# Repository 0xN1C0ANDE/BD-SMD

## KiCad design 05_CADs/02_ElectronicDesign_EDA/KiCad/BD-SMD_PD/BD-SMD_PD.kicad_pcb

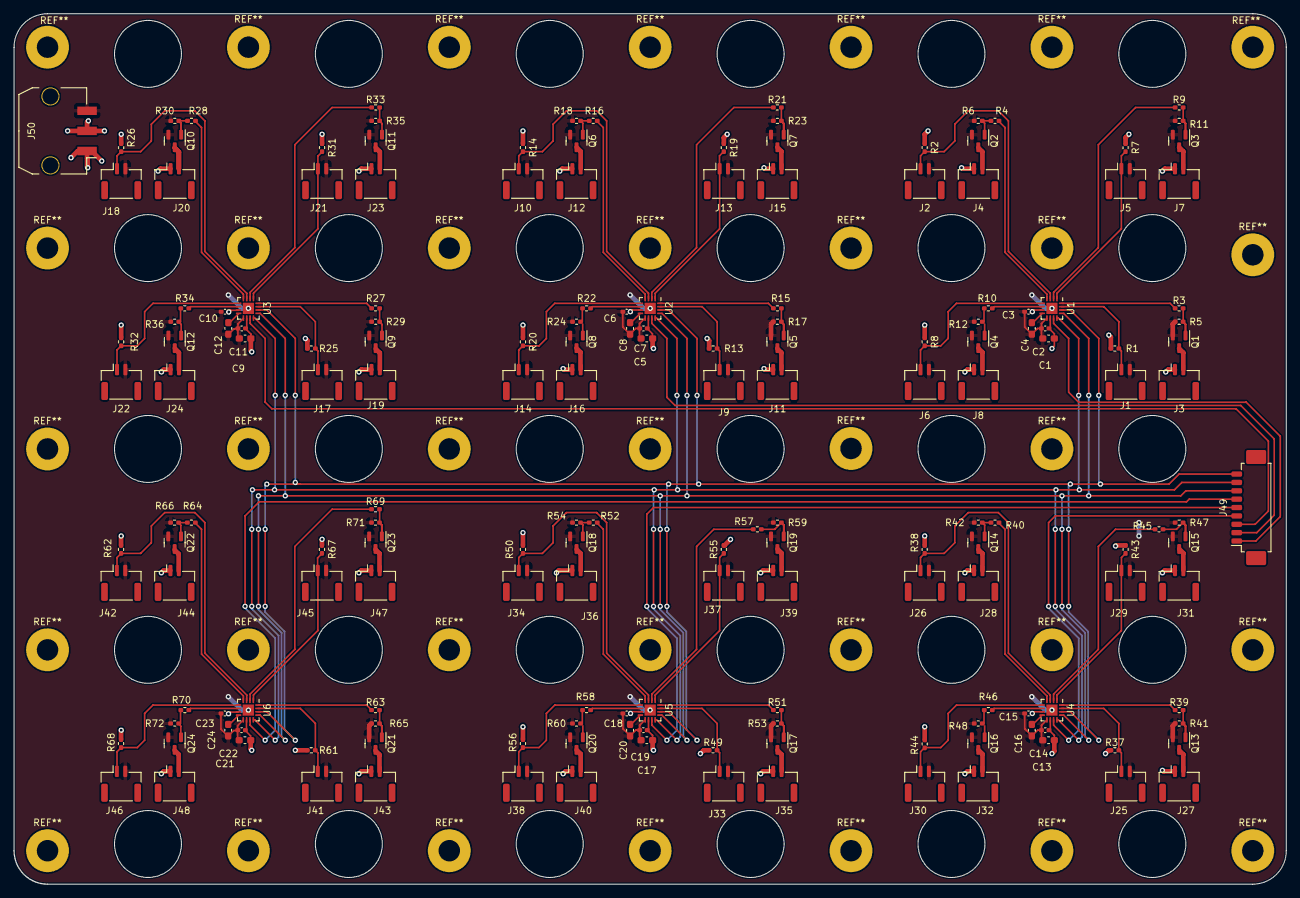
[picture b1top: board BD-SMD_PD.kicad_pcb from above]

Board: 2 copper layers, 190.0 x 130.0 mm, 176 parts (0 on the bottom side), 114 nets.

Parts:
C1, C4, C5, C8, C9, C12, C13, C16, C17, C20, C21, C24: 1u; C_0603_1608Metric_Pad1.08x0.95mm_HandSolder
C2, C3, C6, C7, C10, C11, C14, C15, C18, C19, C22, C23: 100n; C_0402_1005Metric_Pad0.74x0.62mm_HandSolder
J1, J2, J5, J6, J9, J10, J13, J14, J17, J18, J21, J22, J25, J26, J29, J30, J33, J34, J37, J38, J41, J42, J45, J46: Conn_01x02_sens; JST_GH_SM02B-GHS-TB_1x02-1MP_P1.25mm_Horizontal
J3, J4, J7, J8, J11, J12, J15, J16, J19, J20, J23, J24, J27, J28, J31, J32, J35, J36, J39, J40, J43, J44, J47, J48: Conn_01x02_heater; JST_GH_SM02B-GHS-TB_1x02-1MP_P1.25mm_Horizontal
J49: Conn_01x09; Molex_PicoBlade_53261-0971_1x09-1MP_P1.25mm_Horizontal
J50: Conn_01x03; Molex_Micro-Fit_3.0_43650-0310_1x03-1MP_P3.00mm_Horizontal
Q1, Q2, Q3, Q4, Q5, Q6, Q7, Q8, Q9, Q10, Q11, Q12, Q13, Q14, Q15, Q16, Q17, Q18, Q19, Q20, Q21, Q22, Q23, Q24: DMG3418L; SOT-23
R1, R2, R7, R8, R13, R14, R19, R20, R25, R26, R31, R32, R37, R38, R43, R44, R49, R50, R55, R56, R61, R62, R67, R68: 10k; R_0402_1005Metric_Pad0.72x0.64mm_HandSolder
R3, R4, R9, R10, R15, R16, R21, R22, R27, R28, R33, R34, R39, R40, R45, R46, R51, R52, R57, R58, R63, R64, R69, R70: 1k; R_0402_1005Metric_Pad0.72x0.64mm_HandSolder
R5, R6, R11, R12, R17, R18, R23, R24, R29, R30, R35, R36, R41, R42, R47, R48, R53, R54, R59, R60, R65, R66, R71, R72: 100k; R_0402_1005Metric_Pad0.72x0.64mm_HandSolder
U1, U2, U3, U4, U5, U6: ADS7028; WQFN-16-1EP_3x3mm_P0.5mm_EP1.68x1.68mm

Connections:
3.3V: C1.1, C2.1, C3.1, C5.1, C6.1, C7.1, C9.1, C10.1, C11.1, C13.1, C14.1, C15.1, C17.1, C18.1, C19.1, C21.1, C22.1, C23.1, J50.2, R1.1, R2.1, R7.1, R8.1, R13.1, R14.1, R19.1, R20.1, R25.1, R26.1, R31.1, R32.1, R37.1, R38.1, R43.1, R44.1, R49.1, R50.1, R55.1, R56.1, R61.1, R62.1, R67.1, R68.1, U1.7 (AVDD), U1.10 (DVDD), U2.7 (AVDD), U2.10 (DVDD), U3.7 (AVDD), U3.10 (DVDD), U4.7 (AVDD), U4.10 (DVDD), U5.7 (AVDD), U5.10 (DVDD), U6.7 (AVDD), U6.10 (DVDD)
24V: J3.1, J4.1, J7.1, J8.1, J11.1, J12.1, J15.1, J16.1, J19.1, J20.1, J23.1, J24.1, J27.1, J28.1, J31.1, J32.1, J35.1, J36.1, J39.1, J40.1, J43.1, J44.1, J47.1, J48.1, J50.1
/CS_0: J49.1, U1.11 (~CS)
/CS_1: J49.2, U2.11 (~CS)
/CS_2: J49.3, U3.11 (~CS)
/CS_3: J49.4, U4.11 (~CS)
/CS_4: J49.5, U5.11 (~CS)
/CS_5: J49.6, U6.11 (~CS)
/SCLK: J49.7, U1.13 (SCLK), U2.13 (SCLK), U3.13 (SCLK), U4.13 (SCLK), U5.13 (SCLK), U6.13 (SCLK)
/SDI: J49.9, U1.14 (SDI), U2.14 (SDI), U3.14 (SDI), U4.14 (SDI), U5.14 (SDI), U6.14 (SDI)
/SDO: J49.8, U1.12 (SDO), U2.12 (SDO), U3.12 (SDO), U4.12 (SDO), U5.12 (SDO), U6.12 (SDO)
/unit0/AIN0.0: J1.1, R1.2, U1.15 (AIN0)
/unit0/AIN1.0: R3.1, U1.16 (AIN1)
/unit0/AIN2.0: J5.1, R7.2, U1.1 (AIN2)
/unit0/AIN3.0: R9.1, U1.2 (AIN3)
/unit0/AIN4.0: J2.1, R2.2, U1.3 (AIN4)
/unit0/AIN5.0: R4.1, U1.4 (AIN5)
/unit0/AIN6.0: J6.1, R8.2, U1.5 (AIN6)
/unit0/AIN7.0: R10.1, U1.6 (AIN7)
/unit1/AIN0.0: J9.1, R13.2, U2.15 (AIN0)
/unit1/AIN1.0: R15.1, U2.16 (AIN1)
/unit1/AIN2.0: J13.1, R19.2, U2.1 (AIN2)
/unit1/AIN3.0: R21.1, U2.2 (AIN3)
/unit1/AIN4.0: J10.1, R14.2, U2.3 (AIN4)
/unit1/AIN5.0: R16.1, U2.4 (AIN5)
/unit1/AIN6.0: J14.1, R20.2, U2.5 (AIN6)
/unit1/AIN7.0: R22.1, U2.6 (AIN7)
/unit2/AIN0.0: J17.1, R25.2, U3.15 (AIN0)
/unit2/AIN1.0: R27.1, U3.16 (AIN1)
/unit2/AIN2.0: J21.1, R31.2, U3.1 (AIN2)
/unit2/AIN3.0: R33.1, U3.2 (AIN3)
/unit2/AIN4.0: J18.1, R26.2, U3.3 (AIN4)
/unit2/AIN5.0: R28.1, U3.4 (AIN5)
/unit2/AIN6.0: J22.1, R32.2, U3.5 (AIN6)
/unit2/AIN7.0: R34.1, U3.6 (AIN7)
/unit3/AIN0.0: J25.1, R37.2, U4.15 (AIN0)
/unit3/AIN1.0: R39.1, U4.16 (AIN1)
/unit3/AIN2.0: J29.1, R43.2, U4.1 (AIN2)
/unit3/AIN3.0: R45.1, U4.2 (AIN3)
/unit3/AIN4.0: J26.1, R38.2, U4.3 (AIN4)
/unit3/AIN5.0: R40.1, U4.4 (AIN5)
/unit3/AIN6.0: J30.1, R44.2, U4.5 (AIN6)
/unit3/AIN7.0: R46.1, U4.6 (AIN7)
/unit4/AIN0.0: J33.1, R49.2, U5.15 (AIN0)
/unit4/AIN1.0: R51.1, U5.16 (AIN1)
/unit4/AIN2.0: J37.1, R55.2, U5.1 (AIN2)
/unit4/AIN3.0: R57.1, U5.2 (AIN3)
/unit4/AIN4.0: J34.1, R50.2, U5.3 (AIN4)
/unit4/AIN5.0: R52.1, U5.4 (AIN5)
/unit4/AIN6.0: J38.1, R56.2, U5.5 (AIN6)
/unit4/AIN7.0: R58.1, U5.6 (AIN7)
/unit5/AIN0.0: J41.1, R61.2, U6.15 (AIN0)
/unit5/AIN1.0: R63.1, U6.16 (AIN1)
/unit5/AIN2.0: J45.1, R67.2, U6.1 (AIN2)
/unit5/AIN3.0: R69.1, U6.2 (AIN3)
/unit5/AIN4.0: J42.1, R62.2, U6.3 (AIN4)
/unit5/AIN5.0: R64.1, U6.4 (AIN5)
/unit5/AIN6.0: J46.1, R68.2, U6.5 (AIN6)
/unit5/AIN7.0: R70.1, U6.6 (AIN7)
GND: C1.2, C2.2, C3.2, C4.2, C5.2, C6.2, C7.2, C8.2, C9.2, C10.2, C11.2, C12.2, C13.2, C14.2, C15.2, C16.2, C17.2, C18.2, C19.2, C20.2, C21.2, C22.2, C23.2, C24.2, J1.2, J2.2, J5.2, J6.2, J9.2, J10.2, J13.2, J14.2, J17.2, J18.2, J21.2, J22.2, J25.2, J26.2, J29.2, J30.2, J33.2, J34.2, J37.2, J38.2, J41.2, J42.2, J45.2, J46.2, J50.3, Q1.2 (S), Q2.2 (S), Q3.2 (S), Q4.2 (S), Q5.2 (S), Q6.2 (S), Q7.2 (S), Q8.2 (S), Q9.2 (S), Q10.2 (S), Q11.2 (S), Q12.2 (S), Q13.2 (S), Q14.2 (S), Q15.2 (S), Q16.2 (S), Q17.2 (S), Q18.2 (S), Q19.2 (S), Q20.2 (S), Q21.2 (S), Q22.2 (S), Q23.2 (S), Q24.2 (S), R5.2, R6.2, R11.2, R12.2, R17.2, R18.2, R23.2, R24.2, R29.2, R30.2, R35.2, R36.2, R41.2, R42.2, R47.2, R48.2, R53.2, R54.2, R59.2, R60.2, R65.2, R66.2, R71.2, R72.2, U1.9 (GND), U1.17 (GND), U2.9 (GND), U2.17 (GND), U3.9 (GND), U3.17 (GND), U4.9 (GND), U4.17 (GND), U5.9 (GND), U5.17 (GND), U6.9 (GND), U6.17 (GND)
unnamed: C4.1, U1.8 (DECAP)
unnamed: C8.1, U2.8 (DECAP)
unnamed: C12.1, U3.8 (DECAP)
unnamed: C16.1, U4.8 (DECAP)
unnamed: C20.1, U5.8 (DECAP)
unnamed: C24.1, U6.8 (DECAP)
unnamed: J3.2, Q1.3 (D)
unnamed: J4.2, Q2.3 (D)
unnamed: J7.2, Q3.3 (D)
unnamed: J8.2, Q4.3 (D)
unnamed: J11.2, Q5.3 (D)
unnamed: J12.2, Q6.3 (D)
unnamed: J15.2, Q7.3 (D)
unnamed: J16.2, Q8.3 (D)
unnamed: J19.2, Q9.3 (D)
unnamed: J20.2, Q10.3 (D)
unnamed: J23.2, Q11.3 (D)
unnamed: J24.2, Q12.3 (D)
unnamed: J27.2, Q13.3 (D)
unnamed: J28.2, Q14.3 (D)
unnamed: J31.2, Q15.3 (D)
unnamed: J32.2, Q16.3 (D)
unnamed: J35.2, Q17.3 (D)
unnamed: J36.2, Q18.3 (D)
unnamed: J39.2, Q19.3 (D)
unnamed: J40.2, Q20.3 (D)
unnamed: J43.2, Q21.3 (D)
unnamed: J44.2, Q22.3 (D)
unnamed: J47.2, Q23.3 (D)
unnamed: J48.2, Q24.3 (D)
unnamed: Q1.1 (G), R3.2, R5.1
unnamed: Q2.1 (G), R4.2, R6.1
unnamed: Q3.1 (G), R9.2, R11.1
unnamed: Q4.1 (G), R10.2, R12.1
unnamed: Q5.1 (G), R15.2, R17.1
unnamed: Q6.1 (G), R16.2, R18.1
unnamed: Q7.1 (G), R21.2, R23.1
unnamed: Q8.1 (G), R22.2, R24.1
unnamed: Q9.1 (G), R27.2, R29.1
unnamed: Q10.1 (G), R28.2, R30.1
unnamed: Q11.1 (G), R33.2, R35.1
unnamed: Q12.1 (G), R34.2, R36.1
unnamed: Q13.1 (G), R39.2, R41.1
unnamed: Q14.1 (G), R40.2, R42.1
unnamed: Q15.1 (G), R45.2, R47.1
unnamed: Q16.1 (G), R46.2, R48.1
unnamed: Q17.1 (G), R51.2, R53.1
unnamed: Q18.1 (G), R52.2, R54.1
unnamed: Q19.1 (G), R57.2, R59.1
unnamed: Q20.1 (G), R58.2, R60.1
unnamed: Q21.1 (G), R63.2, R65.1
unnamed: Q22.1 (G), R64.2, R66.1
unnamed: Q23.1 (G), R69.2, R71.1
unnamed: Q24.1 (G), R70.2, R72.1

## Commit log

2023-08-08 Commit files
2023-08-08 deleted file
2023-08-08 Production files created
2023-08-08 mods
2023-08-09 mods in bom
